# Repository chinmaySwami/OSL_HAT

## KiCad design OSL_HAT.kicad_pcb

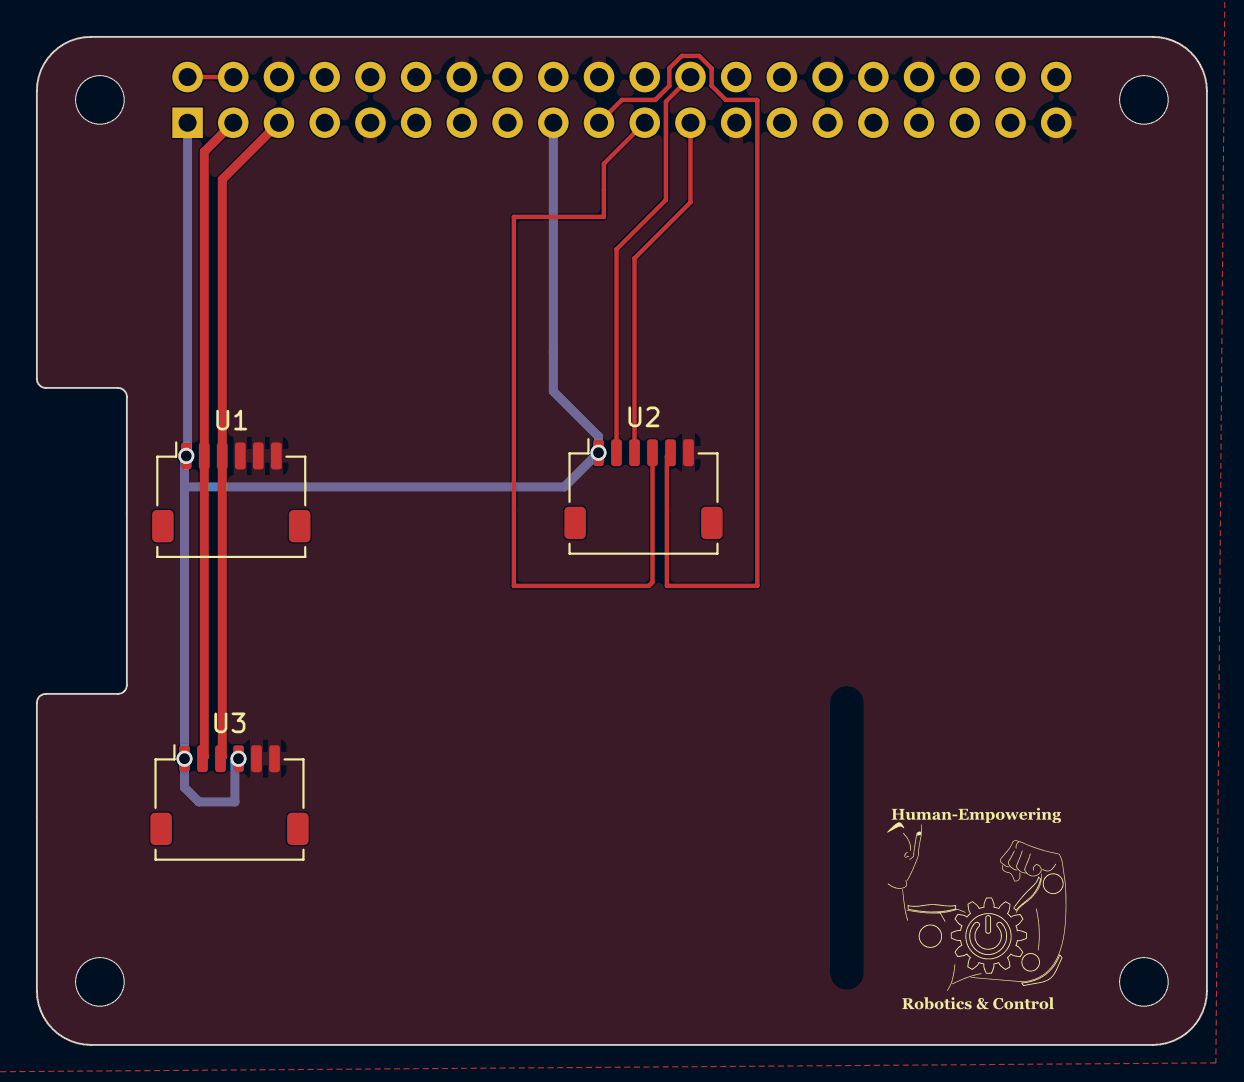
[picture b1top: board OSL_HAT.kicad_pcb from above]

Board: 2 copper layers, 65.0 x 56.0 mm, 8 parts (1 on the bottom side), 9 nets.

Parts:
J1: GPIO; PinSocket_2x20_P2.54mm_Vertical
MH1, MH2, MH3, MH4: MountingHole_2.7mm_M2.5
U1, U2, U3: Molex_Pico-Clasp_202396-0607_1x06-1MP_P1.00mm_Horizontal

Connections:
+3V3: J1.1, J1.17, U1.1 (3v3), U2.1 (3V3), U3.1 (3v3), U3.4 (A1)
+5V: J1.2, J1.4
/GPIO2/SDA1: J1.3, U1.2 (SDA), U3.2 (SDA)
/GPIO3/SCL1: J1.5, U1.3 (SCL), U3.3 (SCL)
/GPIO8/SPI0.CE0: J1.24, U2.2 (CS)
/GPIO9/SPI0.MISO: J1.21, U2.4 (DOUT)
/GPIO10/SPI0.MOSI: J1.19, U2.5 (DIN)
/GPIO11/SPI0.SCLK: J1.23, U2.3 (SCLK)
GND: J1.6, J1.9, J1.14, J1.20, J1.25, J1.30, J1.34, J1.39, U1.4 (A1), U1.5 (A2), U1.6 (GND), U2.6 (GND), U3.5 (A2), U3.6 (GND)

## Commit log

2026-06-16 Initial commit: Completed Raspberry Pi HAT layout
